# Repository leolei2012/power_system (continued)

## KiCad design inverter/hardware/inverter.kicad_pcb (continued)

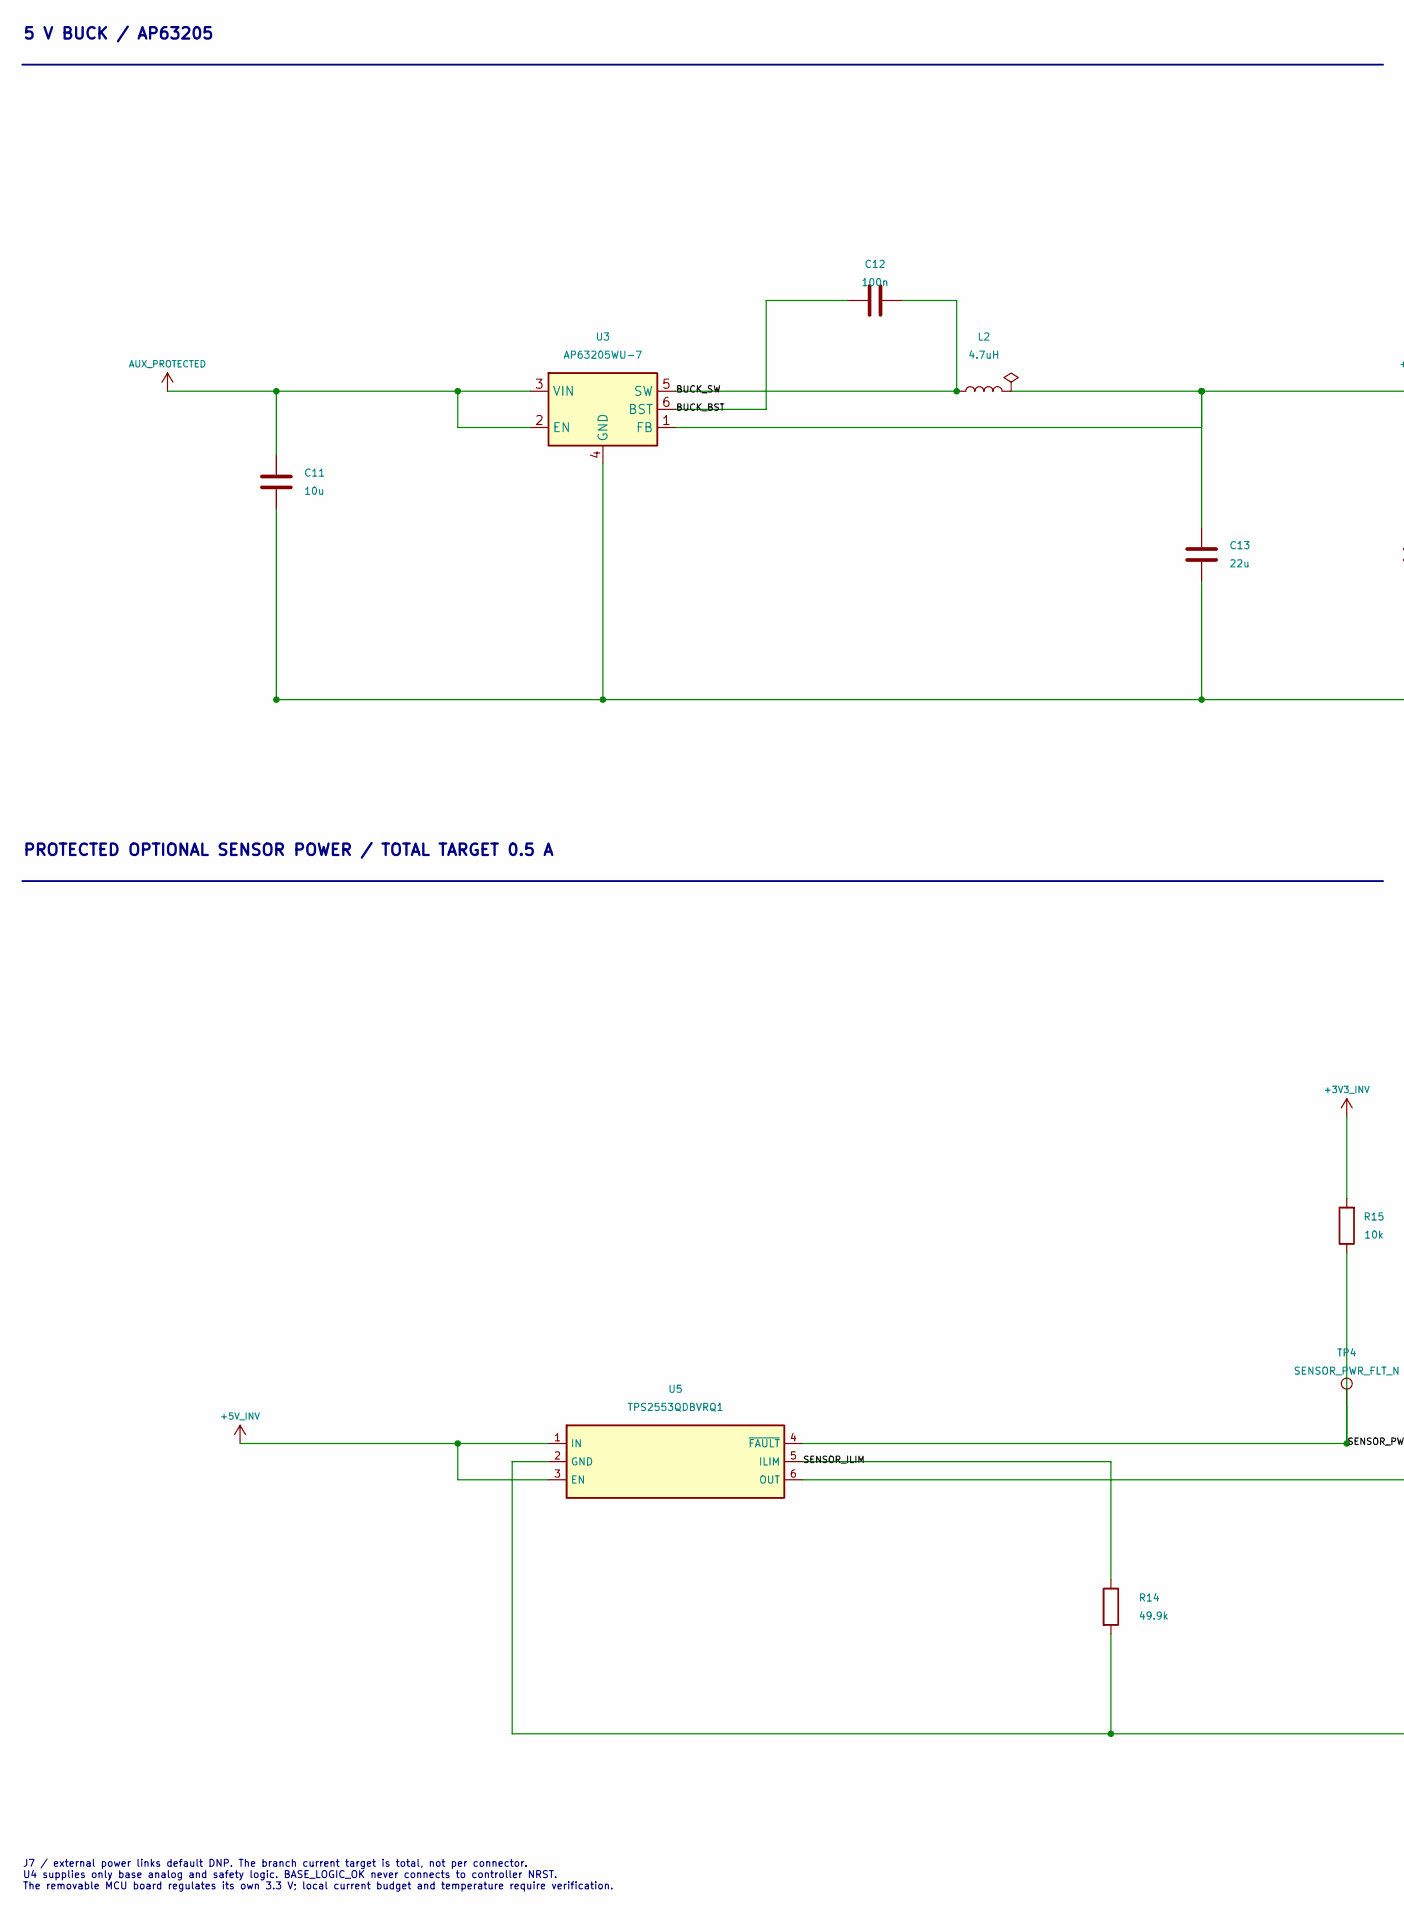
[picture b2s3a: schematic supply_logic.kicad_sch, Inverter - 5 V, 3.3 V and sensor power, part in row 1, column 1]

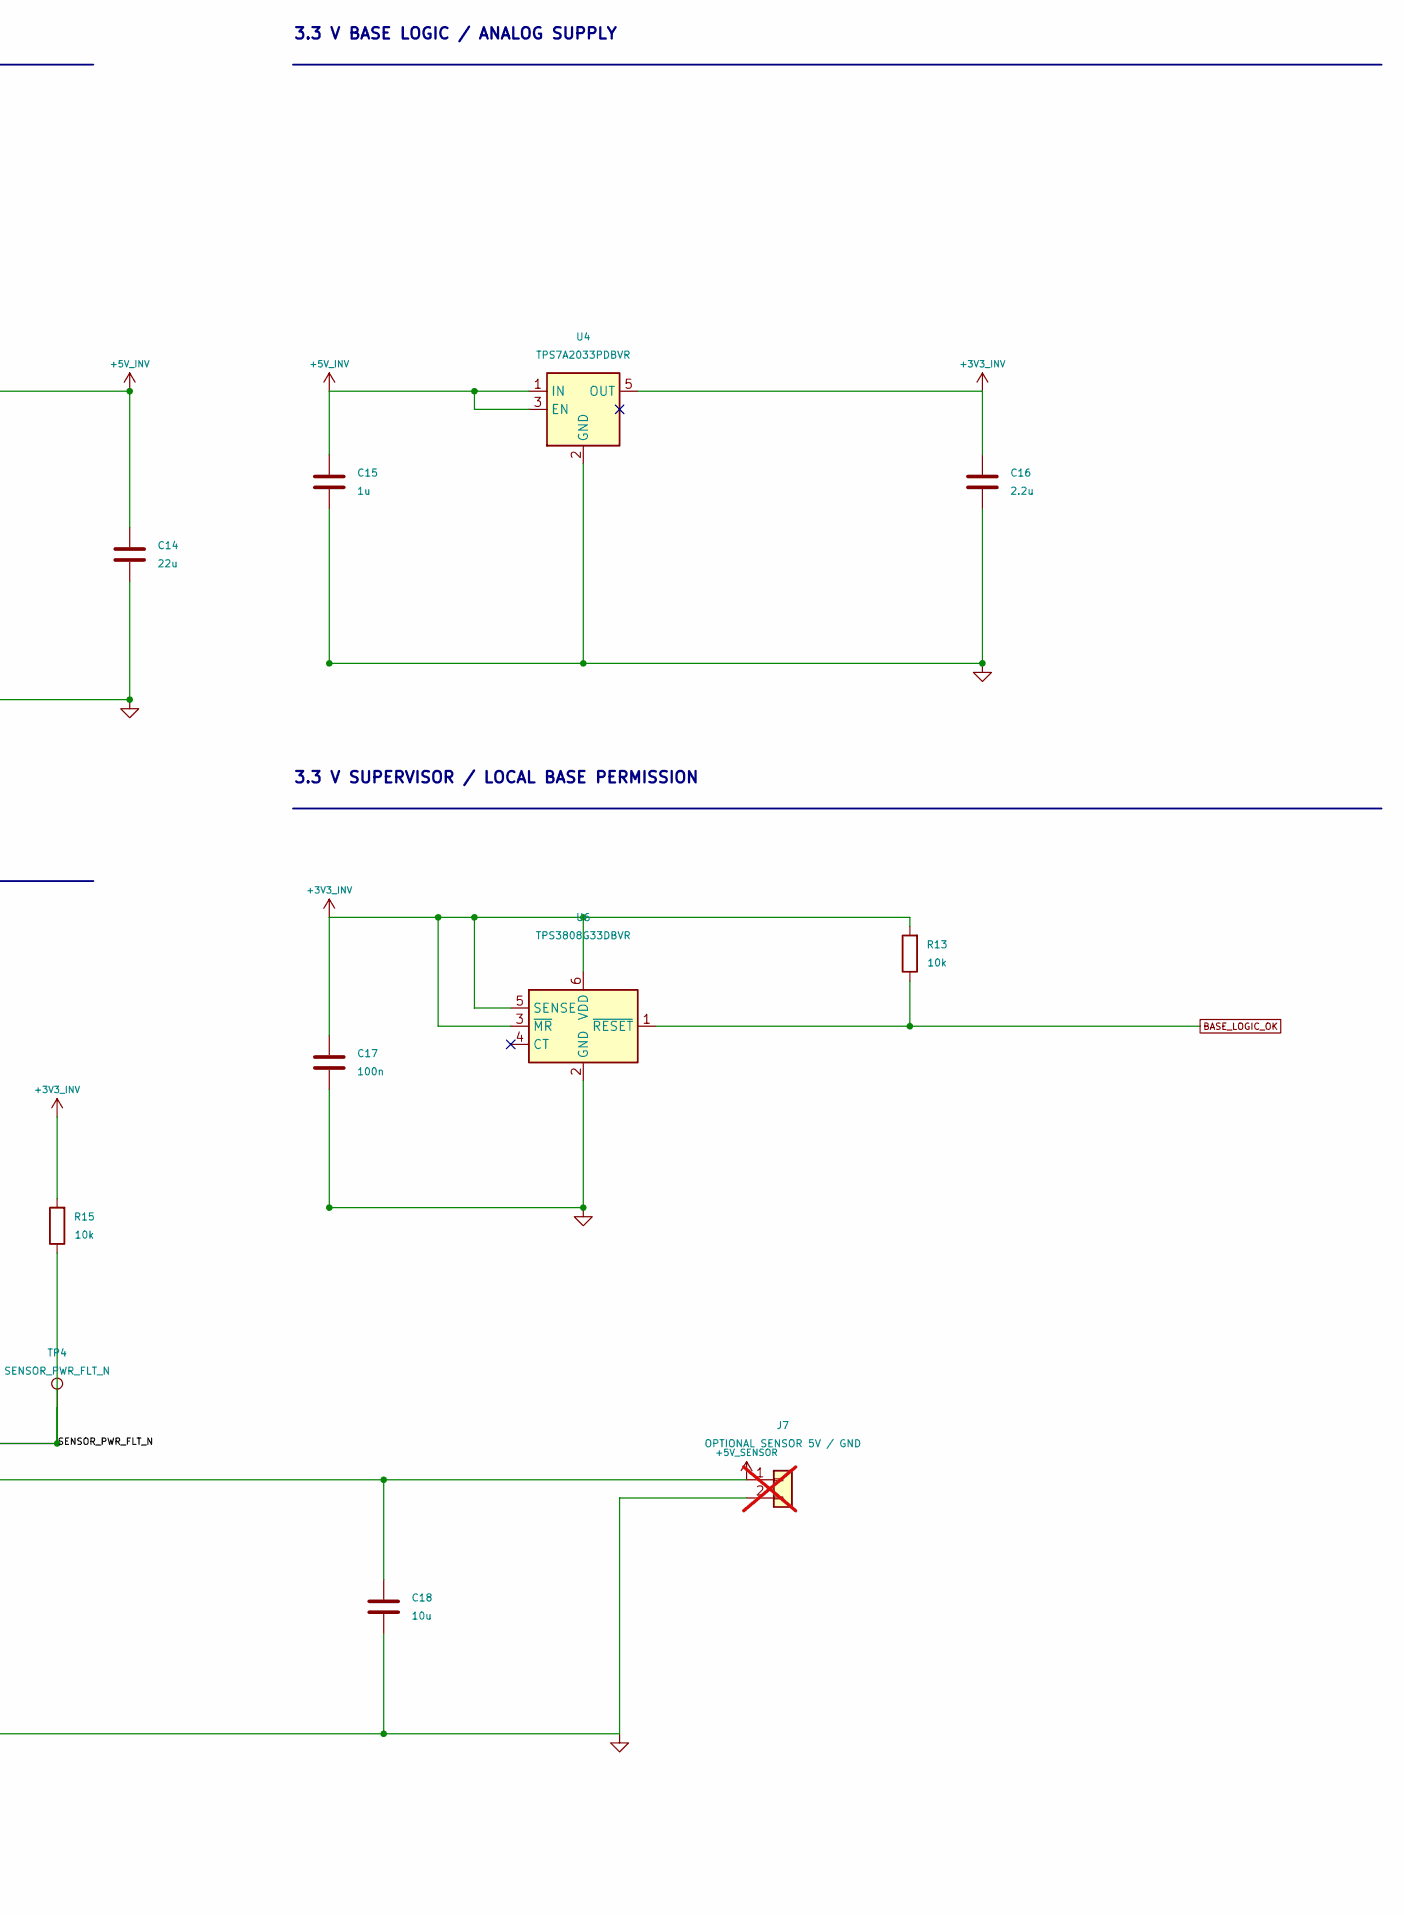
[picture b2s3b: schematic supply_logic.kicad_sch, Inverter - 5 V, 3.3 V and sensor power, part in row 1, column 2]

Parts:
C11: 10u; C_1206_3216Metric; Voltage_Rating 50V; MPN TBD
C12: 100n; C_0603_1608Metric; Voltage_Rating 50V; Tolerance 10%; MPN CC0603KRX7R9BB104
C13, C14: 22u; C_1206_3216Metric; Voltage_Rating 16V; MPN TBD
C15: 1u; C_0603_1608Metric; Voltage_Rating 25V; MPN TBD
C16: 2.2u; C_0603_1608Metric; Voltage_Rating 25V; MPN TBD
C17: 100n; C_0402_1005Metric; Voltage_Rating 25V; MPN TBD
C18: 10u; C_0805_2012Metric; Voltage_Rating 16V; MPN TBD
J7: OPTIONAL SENSOR 5V / GND; HCTL_PZ127_1x02_P1.27mm_Drill0.70mm; MPN PZ127-1-02-Z; not fitted
L2: 4.7uH; L_Sunlord_MWSA0603S; MPN MWSA0603S-4R7MT
R13: 10k; R_0402_1005Metric; Tolerance 1%; MPN TBD
R14: 49.9k; R_0603_1608Metric; Tolerance 1%; MPN TBD
R15: 10k; R_0603_1608Metric; Tolerance 1%; MPN TBD
TP4: SENSOR_PWR_FLT_N; TestPoint_Pad_D1.5mm
U3: AP63205WU-7; TSOT-23-6; MPN AP63205WU-7
U4: TPS7A2033PDBVR; SOT-23-5; MPN TPS7A2033PDBVR
U5: TPS2553QDBVRQ1; SOT-23-6; MPN TPS2553QDBVRQ1
U6: TPS3808G33DBVR; SOT-23-6; MPN TPS3808G33DBVR

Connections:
+3V3_INV: C16.1, C17.1, R13.2, R15.2, U4.5 (OUT), U6.3 (~MR), U6.5 (SENSE), U6.6 (VDD); also elsewhere on the board
+5V_SENSOR: C18.1, J7.1, U5.6 (OUT); also elsewhere on the board
/Logic and sensors/BUCK_BST: C12.1, U3.6 (BST)
/Logic and sensors/BUCK_SW: C12.2, L2.1, U3.5 (SW)
/Logic and sensors/SENSOR_ILIM: R14.1, U5.5 (ILIM)
/Logic and sensors/SENSOR_PWR_FLT_N: R15.1, TP4.1, U5.4 (~FAULT)
AUX_PROTECTED: C11.1, U3.2 (EN), U3.3 (VIN); also elsewhere on the board
BASE_LOGIC_OK: R13.1, U6.1 (~RESET); also elsewhere on the board

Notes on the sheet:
5 V BUCK / AP63205
3.3 V BASE LOGIC / ANALOG SUPPLY
3.3 V SUPERVISOR / LOCAL BASE PERMISSION
PROTECTED OPTIONAL SENSOR POWER / TOTAL TARGET 0.5 A
J7 / external power links default DNP. The branch current target is total, not per connector. U4 supplies only base analog and safety logic. BASE_LOGIC_OK never connects to controller NRST. The removable MCU board regulates its own 3.3 V; local current budget and temperature require verification.

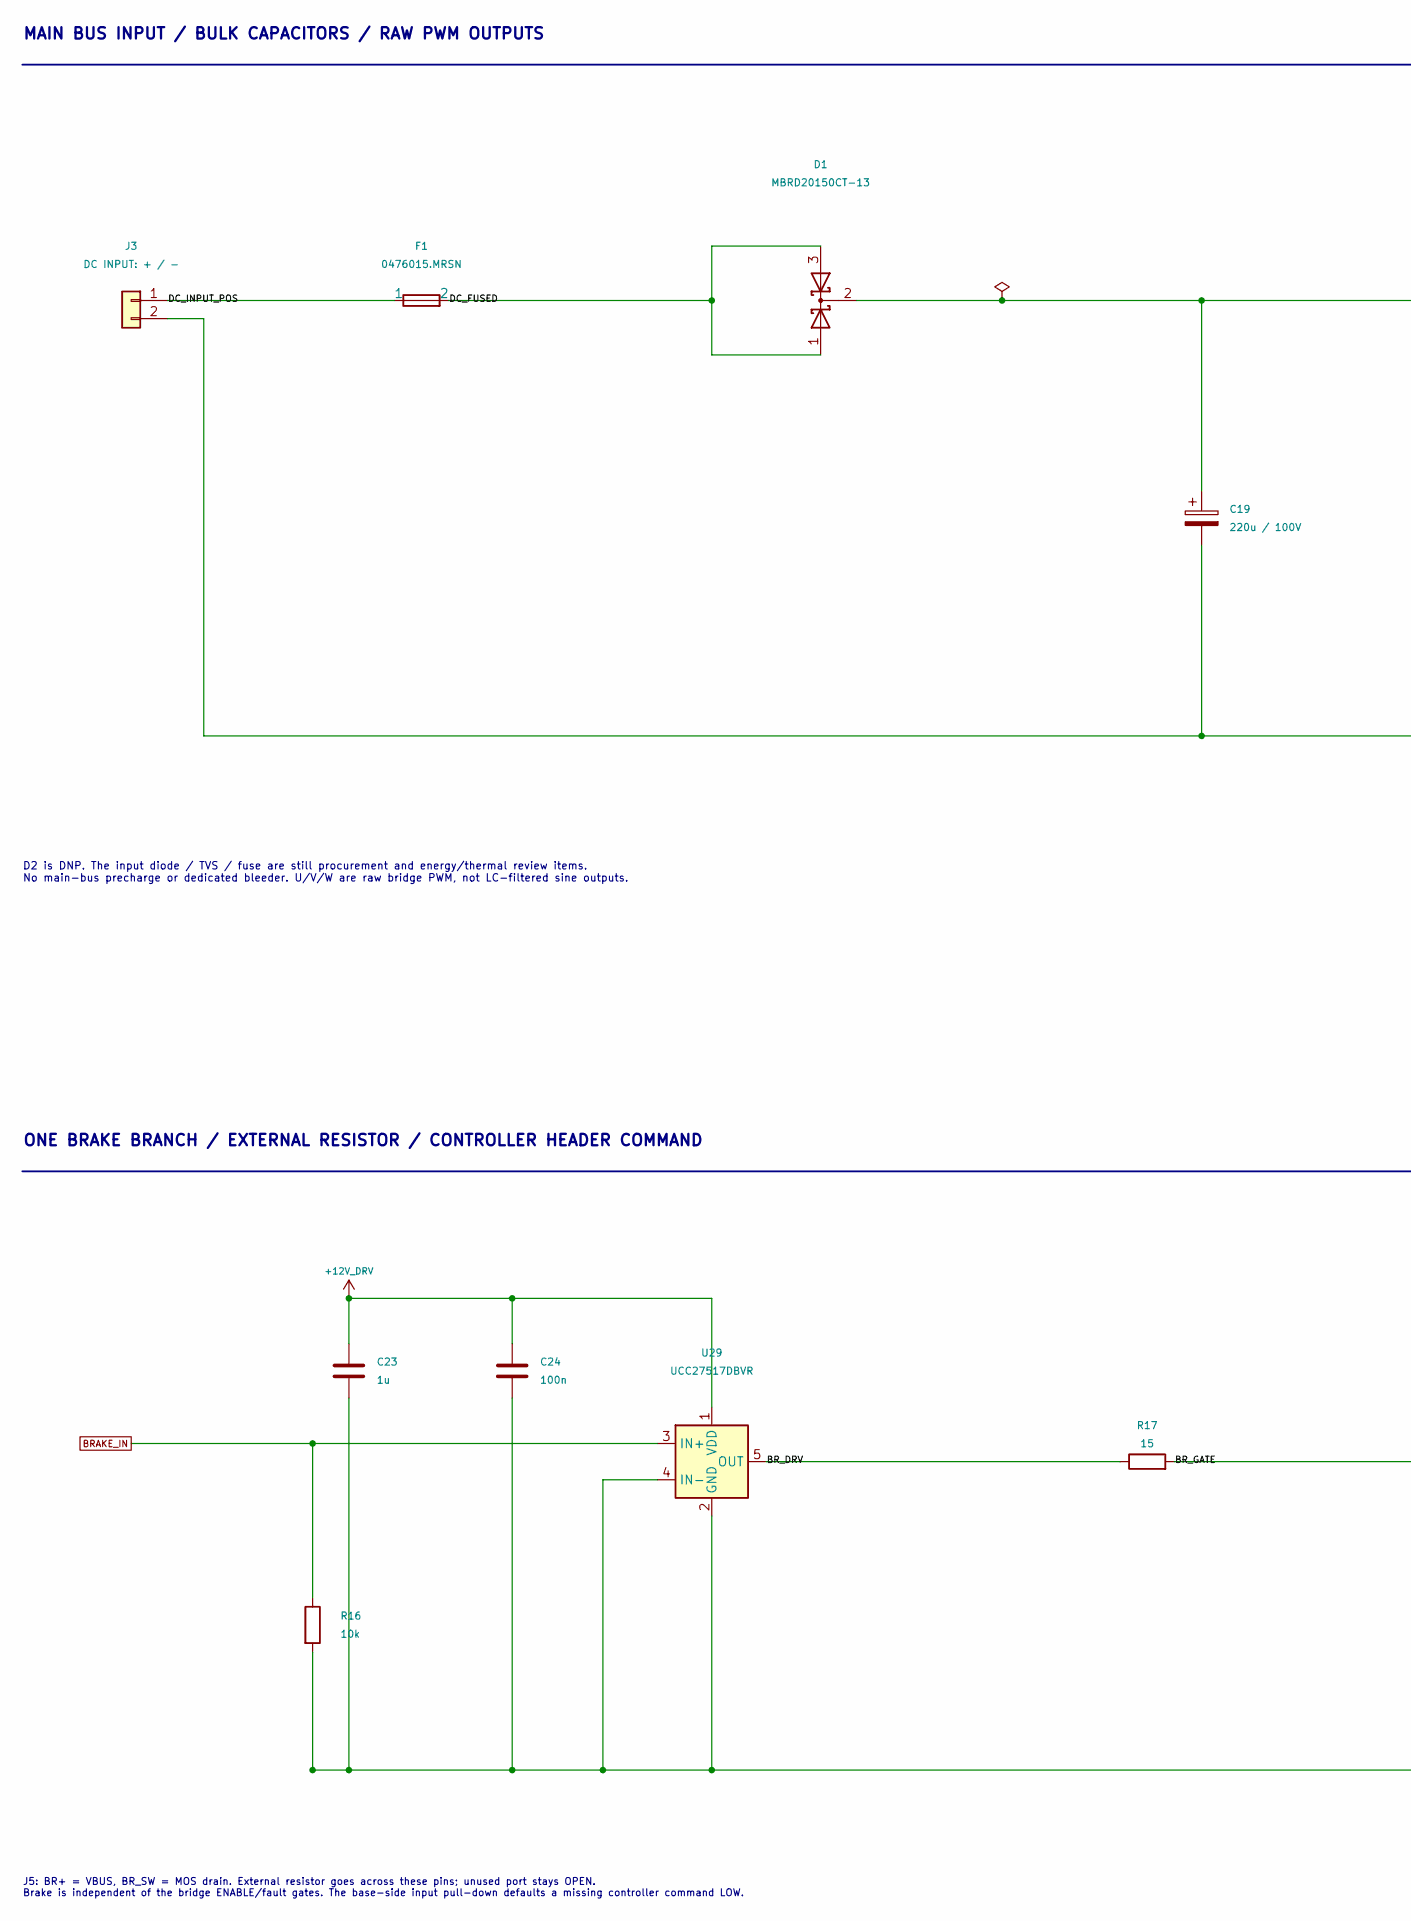
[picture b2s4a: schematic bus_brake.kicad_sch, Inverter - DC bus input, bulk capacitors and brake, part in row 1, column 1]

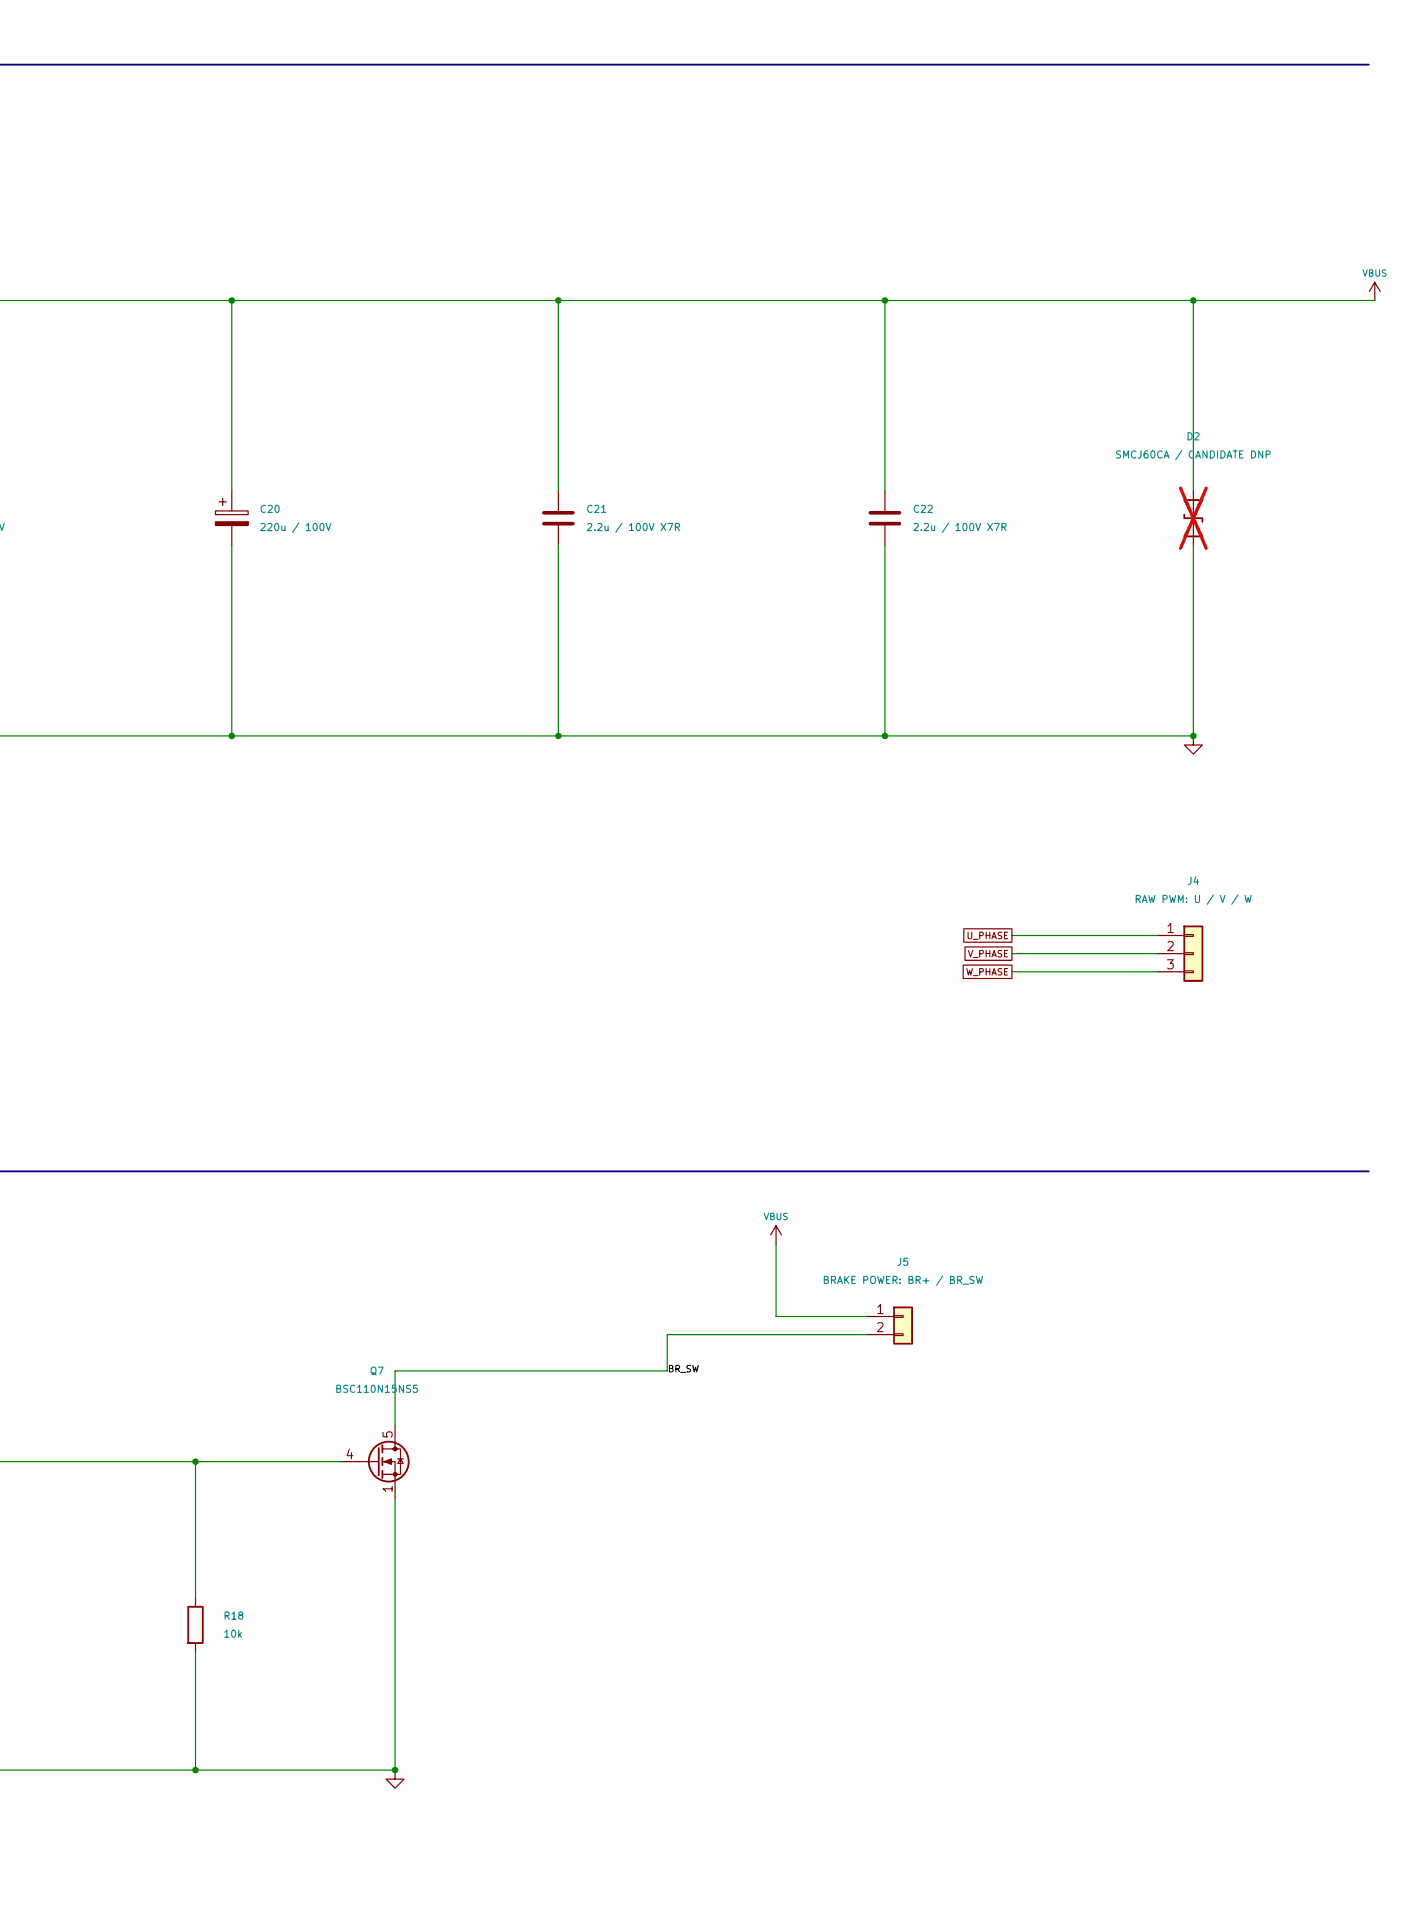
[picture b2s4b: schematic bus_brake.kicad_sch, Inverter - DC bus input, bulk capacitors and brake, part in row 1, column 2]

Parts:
C19, C20: 220u / 100V; CP_Radial_D12.5mm_H25mm_P5.00mm; Voltage 100V; Tolerance 20%; MPN EKYB101ELL221MK25S
C21, C22: 2.2u / 100V X7R; C_1210_3225Metric; Voltage 100V; Tolerance 10%; MPN CS1210KKX7R0BB225
C23: 1u; C_0603_1608Metric; Voltage_Rating 25V; MPN TBD
C24: 100n; C_0603_1608Metric; Voltage_Rating 50V; Tolerance 10%; MPN CC0603KRX7R9BB104
D1: MBRD20150CT-13; Diodes_MBRD20150CT_TO252_Recommended; MPN MBRD20150CT-13
D2: SMCJ60CA / CANDIDATE DNP; SMC_DO-214AB_Bidirectional; MPN SMCJ60CA; not fitted
F1: 0476015.MRSN; Littelfuse_NANO2_451_476_Pad1.96x3.15mm_Gap2.95mm; MPN 0476015.MRSN
J3: DC INPUT: + / -; WireSolder_2P_P6.00mm_D2.00mm; MPN PCB solder holes / wire assembly
J4: RAW PWM: U / V / W; WireSolder_3P_P15.00mm_D2.00mm; MPN PCB solder holes / wire assembly
J5: BRAKE POWER: BR+ / BR_SW; WireSolder_2P_P6.00mm_D2.00mm; MPN PCB solder holes / wire assembly
Q7: BSC110N15NS5; Infineon_BSC110N15NS5_PG-TDSON8_8PhysicalPins; MPN BSC110N15NS5ATMA1
R16, R18: 10k; R_0603_1608Metric; Tolerance 1%; MPN TBD
R17: 15; R_0805_2012Metric; Tolerance 1%; MPN TBD
U29: UCC27517DBVR; SOT-23-5; MPN UCC27517DBVR

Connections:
+12V_DRV: C23.1, C24.1, U29.1 (VDD); also elsewhere on the board
/Bus and brake/BR_DRV: R17.1, U29.5 (OUT)
/Bus and brake/BR_GATE: Q7.4 (G), R17.2, R18.1
/Bus and brake/BR_SW: J5.2, Q7.5 (D), Q7.6 (D), Q7.7 (D), Q7.8 (D)
/Bus and brake/DC_FUSED: D1.1 (A1), D1.3 (A2), F1.2
/Bus and brake/DC_INPUT_POS: F1.1, J3.1
BRAKE_IN: R16.1, U29.3 (IN+); also elsewhere on the board
U_PHASE: J4.1; also elsewhere on the board
VBUS: C19.1, C20.1, C21.1, C22.1, D1.2 (K), D2.1 (A1), J5.1; also elsewhere on the board
V_PHASE: J4.2; also elsewhere on the board
W_PHASE: J4.3; also elsewhere on the board

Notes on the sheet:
MAIN BUS INPUT / BULK CAPACITORS / RAW PWM OUTPUTS
D2 is DNP. The input diode / TVS / fuse are still procurement and energy/thermal review items. No main-bus precharge or dedicated bleeder. U/V/W are raw bridge PWM, not LC-filtered sine outputs.
ONE BRAKE BRANCH / EXTERNAL RESISTOR / CONTROLLER HEADER COMMAND
J5: BR+ = VBUS, BR_SW = MOS drain. External resistor goes across these pins; unused port stays OPEN. Brake is independent of the bridge ENABLE/fault gates. The base-side input pull-down defaults a missing controller command LOW.

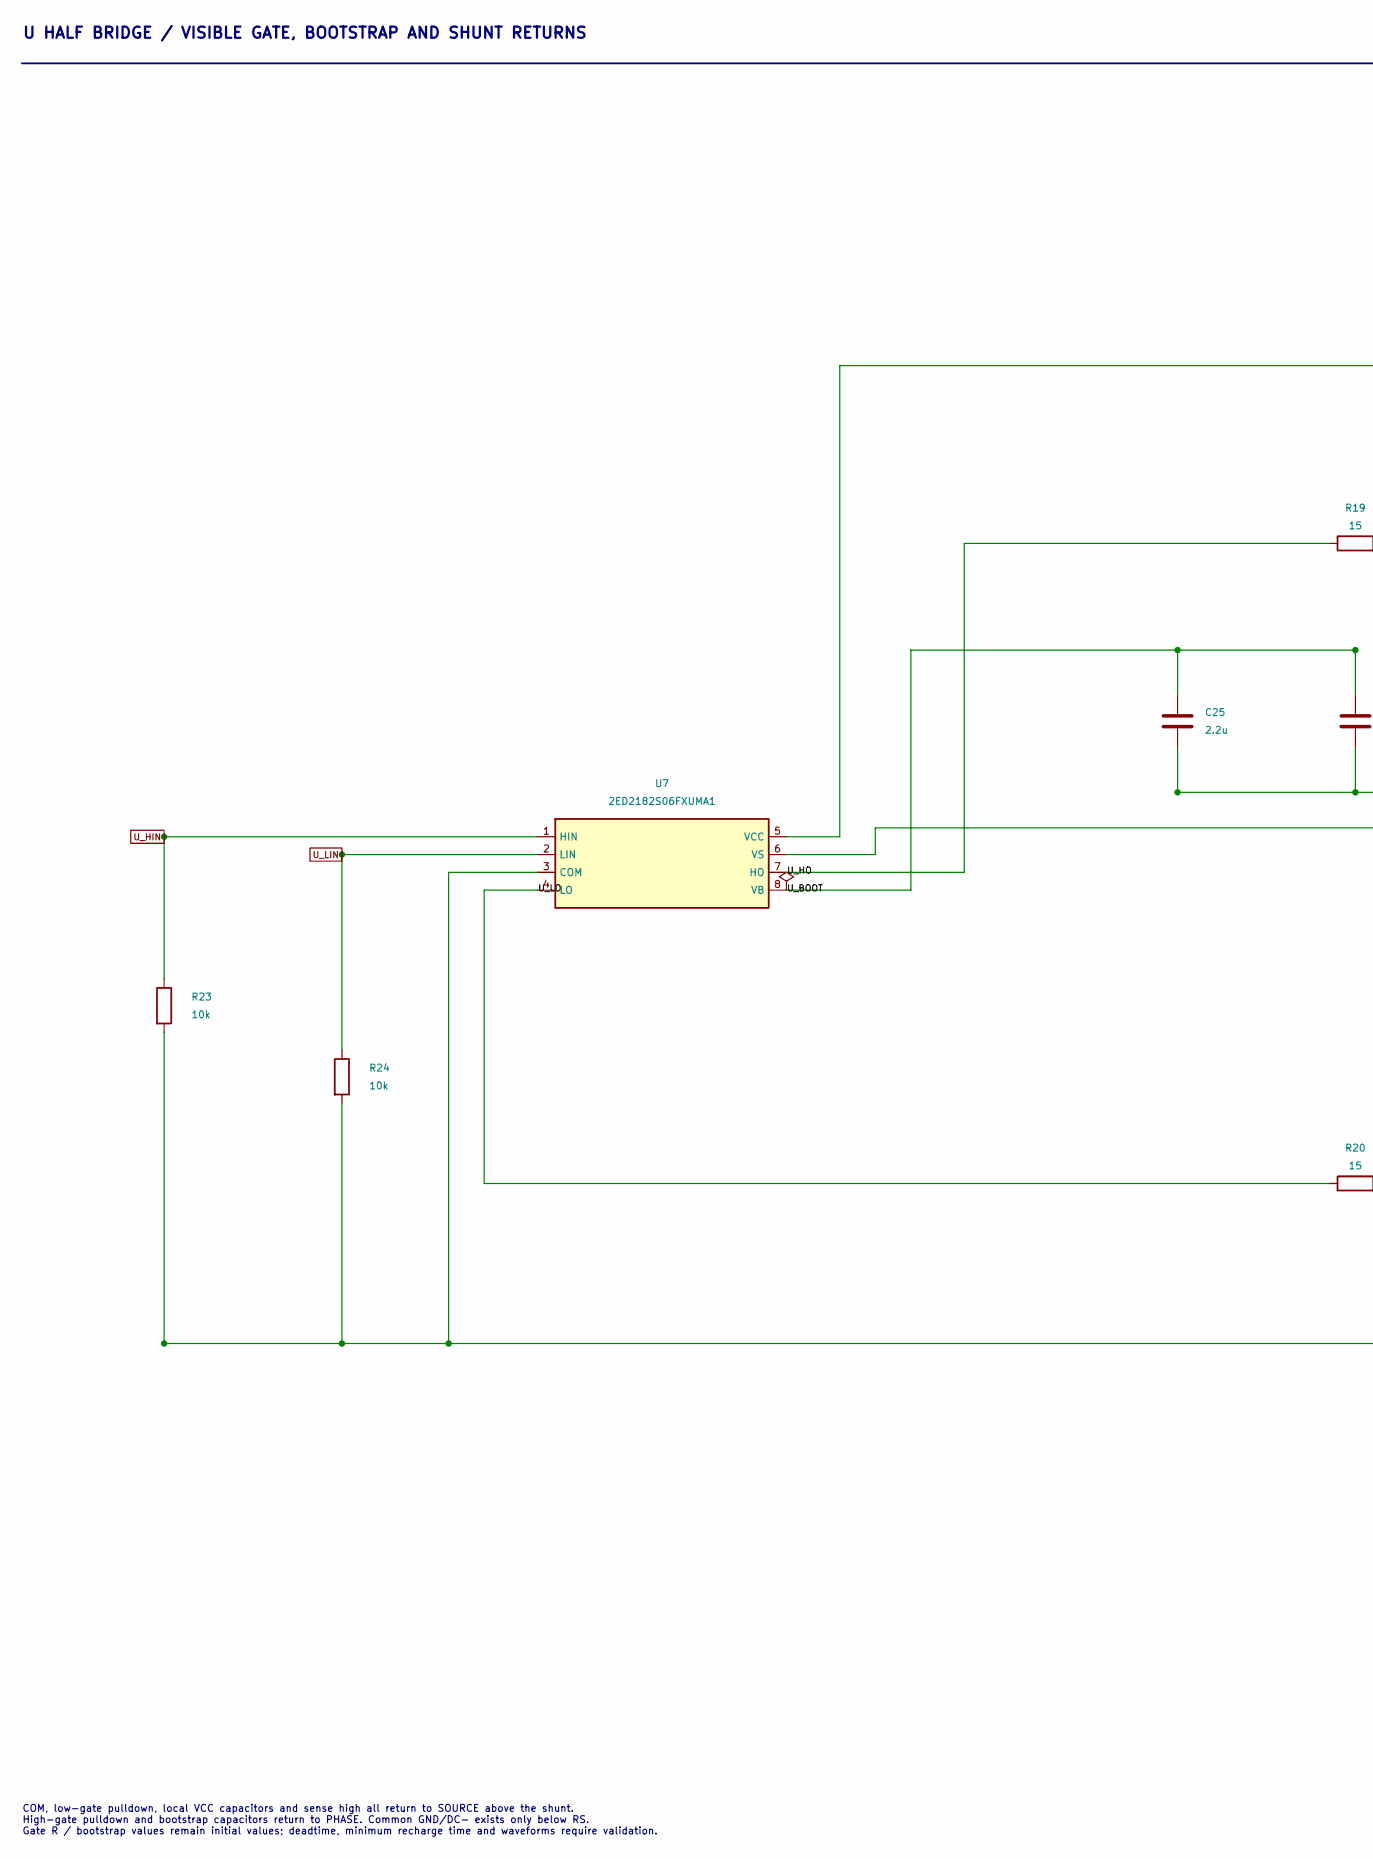
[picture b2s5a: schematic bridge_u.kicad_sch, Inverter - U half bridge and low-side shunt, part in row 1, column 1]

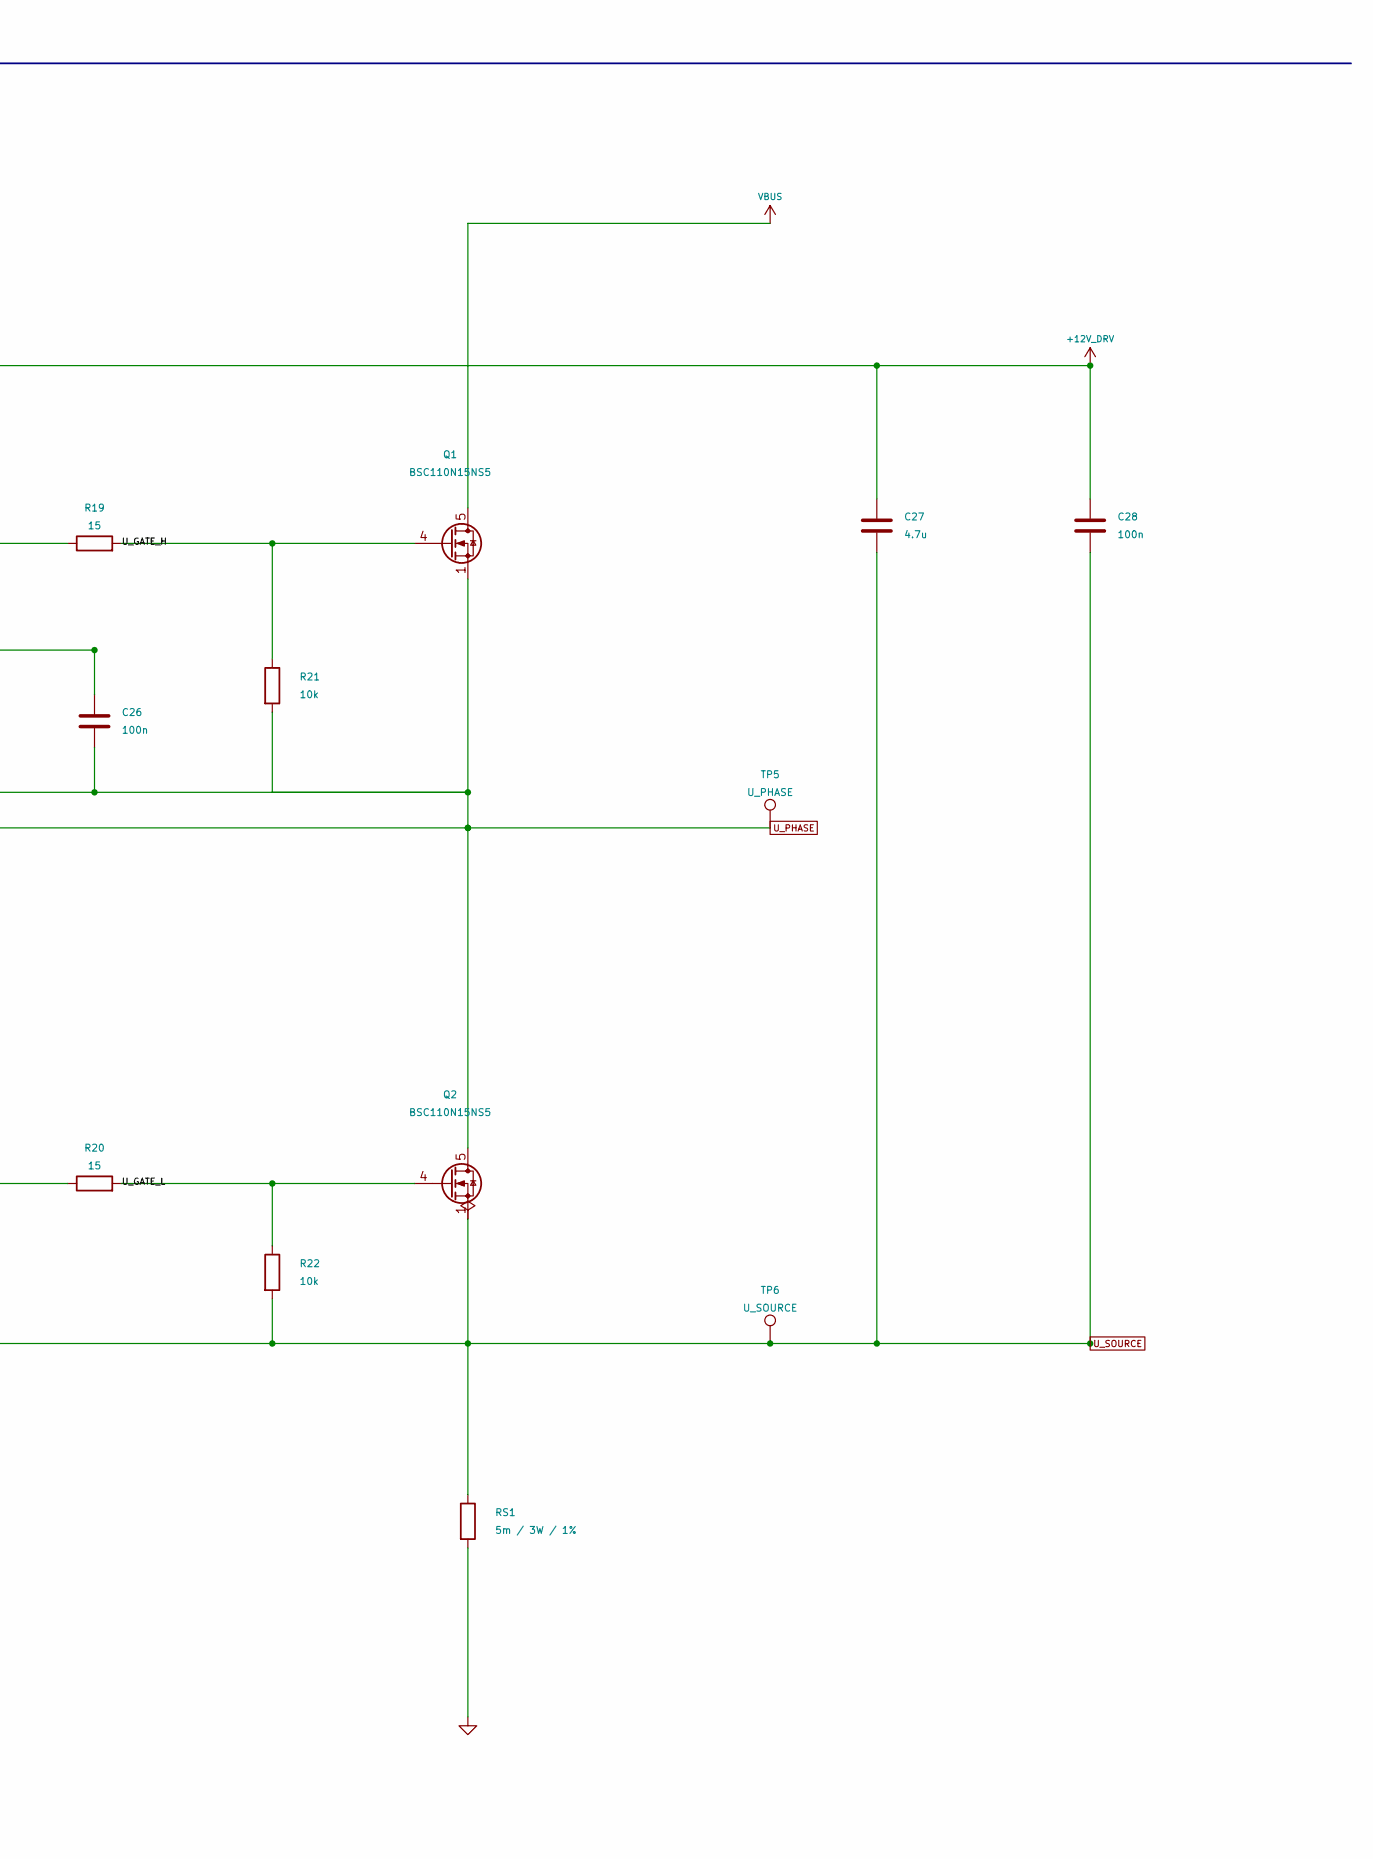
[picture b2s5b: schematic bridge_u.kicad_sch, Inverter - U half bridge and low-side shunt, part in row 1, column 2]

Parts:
C25: 2.2u; C_1206_3216Metric; Voltage_Rating 25V; MPN TBD
C26, C28: 100n; C_0603_1608Metric; Voltage_Rating 50V; Tolerance 10%; MPN CC0603KRX7R9BB104
C27: 4.7u; C_0805_2012Metric; Voltage_Rating 25V; MPN TBD
Q1, Q2: BSC110N15NS5; Infineon_BSC110N15NS5_PG-TDSON8_8PhysicalPins; MPN BSC110N15NS5ATMA1
R19, R20: 15; R_0805_2012Metric; Tolerance 1%; MPN TBD
R21, R22, R23, R24: 10k; R_0603_1608Metric; Tolerance 1%; MPN TBD
RS1: 5m / 3W / 1%; Milliohm_HoJLR2512_Pad2.1x4.0mm_Gap4.1mm; MPN HoJLR2512-3W-5mR-1%
TP5: U_PHASE; TestPoint_Pad_D1.5mm
TP6: U_SOURCE; TestPoint_Pad_D1.5mm
U7: 2ED2182S06FXUMA1; SOIC-8_3.9x4.9mm_P1.27mm; MPN 2ED2182S06FXUMA1

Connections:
+12V_DRV: C27.1, C28.1, U7.5 (VCC); also elsewhere on the board
/U half bridge/U_BOOT: C25.1, C26.1, U7.8 (VB)
/U half bridge/U_GATE_H: Q1.4 (G), R19.2, R21.1
/U half bridge/U_GATE_L: Q2.4 (G), R20.2, R22.1
/U half bridge/U_HO: R19.1, U7.7 (HO)
/U half bridge/U_LO: R20.1, U7.4 (LO)
U_HIN: R23.1, U7.1 (HIN); also elsewhere on the board
U_LIN: R24.1, U7.2 (LIN); also elsewhere on the board
U_PHASE: C25.2, C26.2, Q1.1 (S), Q1.2 (S), Q1.3 (S), Q2.5 (D), Q2.6 (D), Q2.7 (D), Q2.8 (D), R21.2, TP5.1, U7.6 (VS); also elsewhere on the board
U_SOURCE: C27.2, C28.2, Q2.1 (S), Q2.2 (S), Q2.3 (S), R22.2, R23.2, R24.2, RS1.1, TP6.1, U7.3 (COM); also elsewhere on the board
VBUS: Q1.5 (D), Q1.6 (D), Q1.7 (D), Q1.8 (D); also elsewhere on the board

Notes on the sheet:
U HALF BRIDGE / VISIBLE GATE, BOOTSTRAP AND SHUNT RETURNS
COM, low-gate pulldown, local VCC capacitors and sense high all return to SOURCE above the shunt. High-gate pulldown and bootstrap capacitors return to PHASE. Common GND/DC- exists only below RS. Gate R / bootstrap values remain initial values; deadtime, minimum recharge time and waveforms require 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
